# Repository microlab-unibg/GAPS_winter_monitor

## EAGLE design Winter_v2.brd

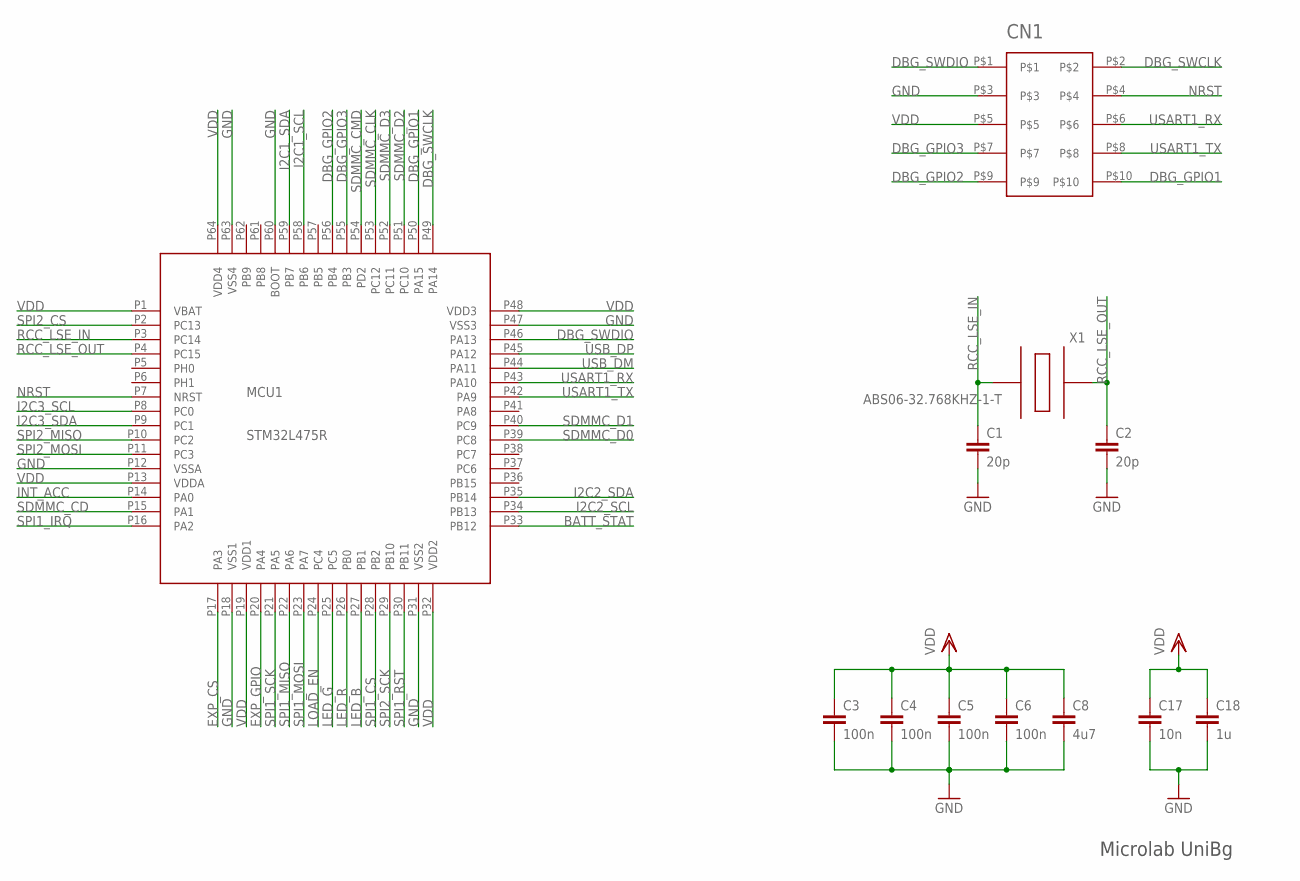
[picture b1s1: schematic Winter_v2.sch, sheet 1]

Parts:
C1, C2: 20p; C0402
C3, C4, C5, C6: 100n; C0402
C8: 4u7; C0402
C17: 10n; C0402
C18: 1u; C0402
CN1: FTSH-105TO; FTSH-105-XX
MCU1: STM32L475R; LQFP64
X1: ABS06-32.768KHZ-1-T; ABS06

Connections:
BATT_STAT: MCU1.P33 (PB12); also elsewhere on the board
DBG_GPIO1: CN1.P$10, MCU1.P50 (PA15)
DBG_GPIO2: CN1.P$9, MCU1.P56 (PB4)
DBG_GPIO3: CN1.P$7, MCU1.P55 (PB3)
DBG_SWCLK: CN1.P$2, MCU1.P49 (PA14)
DBG_SWDIO: CN1.P$1, MCU1.P46 (PA13)
EXP_CS: MCU1.P17 (PA3); also elsewhere on the board
EXP_GPIO: MCU1.P20 (PA4); also elsewhere on the board
GND: C1.P$2 (2), C2.P$2 (2), C3.P$2 (2), C4.P$2 (2), C5.P$2 (2), C6.P$2 (2), C8.P$2 (2), C17.P$2 (2), C18.P$2 (2), CN1.P$3, MCU1.P12 (VSSA), MCU1.P18 (VSS1), MCU1.P31 (VSS2), MCU1.P47 (VSS3), MCU1.P60 (BOOT), MCU1.P63 (VSS4); also elsewhere on the board
I2C1_SCL: MCU1.P58 (PB6); also elsewhere on the board
I2C1_SDA: MCU1.P59 (PB7); also elsewhere on the board
I2C2_SCL: MCU1.P34 (PB13); also elsewhere on the board
I2C2_SDA: MCU1.P35 (PB14); also elsewhere on the board
I2C3_SCL: MCU1.P8 (PC0); also elsewhere on the board
I2C3_SDA: MCU1.P9 (PC1); also elsewhere on the board
INT_ACC: MCU1.P14 (PA0); also elsewhere on the board
LED_B: MCU1.P27 (PB1); also elsewhere on the board
LED_G: MCU1.P25 (PC5); also elsewhere on the board
LED_R: MCU1.P26 (PB0); also elsewhere on the board
LOAD_EN: MCU1.P24 (PC4); also elsewhere on the board
NRST: CN1.P$4, MCU1.P7 (NRST)
RCC_LSE_IN: C1.P$1 (1), MCU1.P3 (PC14), X1.P1
RCC_LSE_OUT: C2.P$1 (1), MCU1.P4 (PC15), X1.P2
SDMMC_CD: MCU1.P15 (PA1); also elsewhere on the board
SDMMC_CLK: MCU1.P53 (PC12); also elsewhere on the board
SDMMC_CMD: MCU1.P54 (PD2); also elsewhere on the board
SDMMC_D0: MCU1.P39 (PC8); also elsewhere on the board
SDMMC_D1: MCU1.P40 (PC9); also elsewhere on the board
SDMMC_D2: MCU1.P51 (PC10); also elsewhere on the board
SDMMC_D3: MCU1.P52 (PC11); also elsewhere on the board
SPI1_CS: MCU1.P28 (PB2); also elsewhere on the board
SPI1_IRQ: MCU1.P16 (PA2); also elsewhere on the board
SPI1_MISO: MCU1.P22 (PA6); also elsewhere on the board
SPI1_MOSI: MCU1.P23 (PA7); also elsewhere on the board
SPI1_RST: MCU1.P30 (PB11); also elsewhere on the board
SPI1_SCK: MCU1.P21 (PA5); also elsewhere on the board
SPI2_CS: MCU1.P2 (PC13); also elsewhere on the board
SPI2_MISO: MCU1.P10 (PC2); also elsewhere on the board
SPI2_MOSI: MCU1.P11 (PC3); also elsewhere on the board
SPI2_SCK: MCU1.P29 (PB10); also elsewhere on the board
USART1_RX: CN1.P$6, MCU1.P43 (PA10)
USART1_TX: CN1.P$8, MCU1.P42 (PA9)
USB_DM: MCU1.P44 (PA11); also elsewhere on the board
USB_DP: MCU1.P45 (PA12); also elsewhere on the board
VDD: C3.P$1 (1), C4.P$1 (1), C5.P$1 (1), C6.P$1 (1), C8.P$1 (1), C17.P$1 (1), C18.P$1 (1), CN1.P$5, MCU1.P1 (VBAT), MCU1.P13 (VDDA), MCU1.P19 (VDD1), MCU1.P32 (VDD2), MCU1.P48 (VDD3), MCU1.P64 (VDD4); also elsewhere on the board

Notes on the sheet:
Microlab UniBg

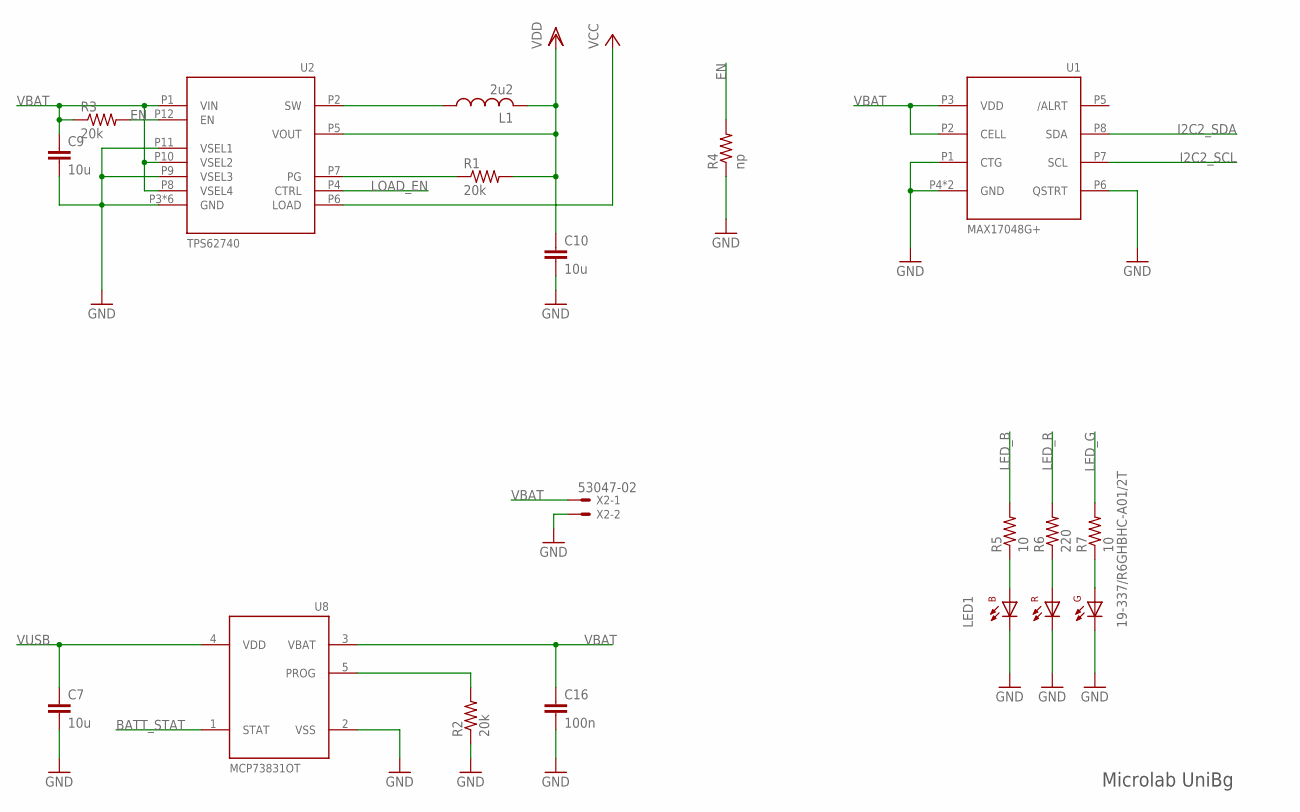
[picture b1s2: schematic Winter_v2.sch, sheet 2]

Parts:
C7, C9, C10: 10u; C0603
C16: 100n; C0402
L1: 2u2; C01005
LED1: 19-337/R6GHBHC-A01/2T
R1, R2, R3: 20k; 0402
R4: np; 0402
R5, R7: 10; 0402
R6: 220; 0402
U1: MAX17048G+; TDFN8-2X2
U2: TPS62740; R-PWSON-N12
U8: MCP73831OT; SOT23-5L
X2: 53047-02

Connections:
BATT_STAT: U8.1 (STAT); also elsewhere on the board
EN: R3.P$2 (2), R4.P$2 (2), U2.P12 (EN)
GND: C7.P$2 (2), C9.P$2 (2), C10.P$2 (2), C16.P$2 (2), LED1.P$1 (CB), LED1.P$2 (CR), LED1.P$3 (CG), R2.P$1 (1), R4.P$1 (1), U1.P1 (CTG), U1.P4 (GND), U1.P6 (QSTRT), U1.P9 (GND), U2.P3 (GND), U2.P9 (VSEL3), U2.P11 (VSEL1), U2.PG1 (GND), U2.PG2 (GND), U2.PG3 (GND), U2.PG4 (GND), U2.PG5 (GND), U8.2 (VSS), X2.2; also elsewhere on the board
I2C2_SCL: U1.P7 (SCL); also elsewhere on the board
I2C2_SDA: U1.P8 (SDA); also elsewhere on the board
LED_B: R5.P$2 (2); also elsewhere on the board
LED_G: R7.P$2 (2); also elsewhere on the board
LED_R: R6.P$2 (2); also elsewhere on the board
LOAD_EN: U2.P4 (CTRL); also elsewhere on the board
unnamed: L1.P$1 (1), U2.P2 (SW)
unnamed: R1.P$1 (1), U2.P7 (PG)
unnamed: LED1.P$4 (AB), R5.P$1 (1)
unnamed: LED1.P$5 (AR), R6.P$1 (1)
unnamed: LED1.P$6 (AG), R7.P$1 (1)
unnamed: R2.P$2 (2), U8.5 (PROG)
VBAT: C9.P$1 (1), C16.P$1 (1), R3.P$1 (1), U1.P2 (CELL), U1.P3 (VDD), U2.P1 (VIN), U2.P8 (VSEL4), U2.P10 (VSEL2), U8.3 (VBAT), X2.1; also elsewhere on the board
VCC: U2.P6 (LOAD); also elsewhere on the board
VDD: C10.P$1 (1), L1.P$2 (2), R1.P$2 (2), U2.P5 (VOUT); also elsewhere on the board
VUSB: C7.P$1 (1), U8.4 (VDD); also elsewhere on the board

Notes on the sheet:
Microlab UniBg

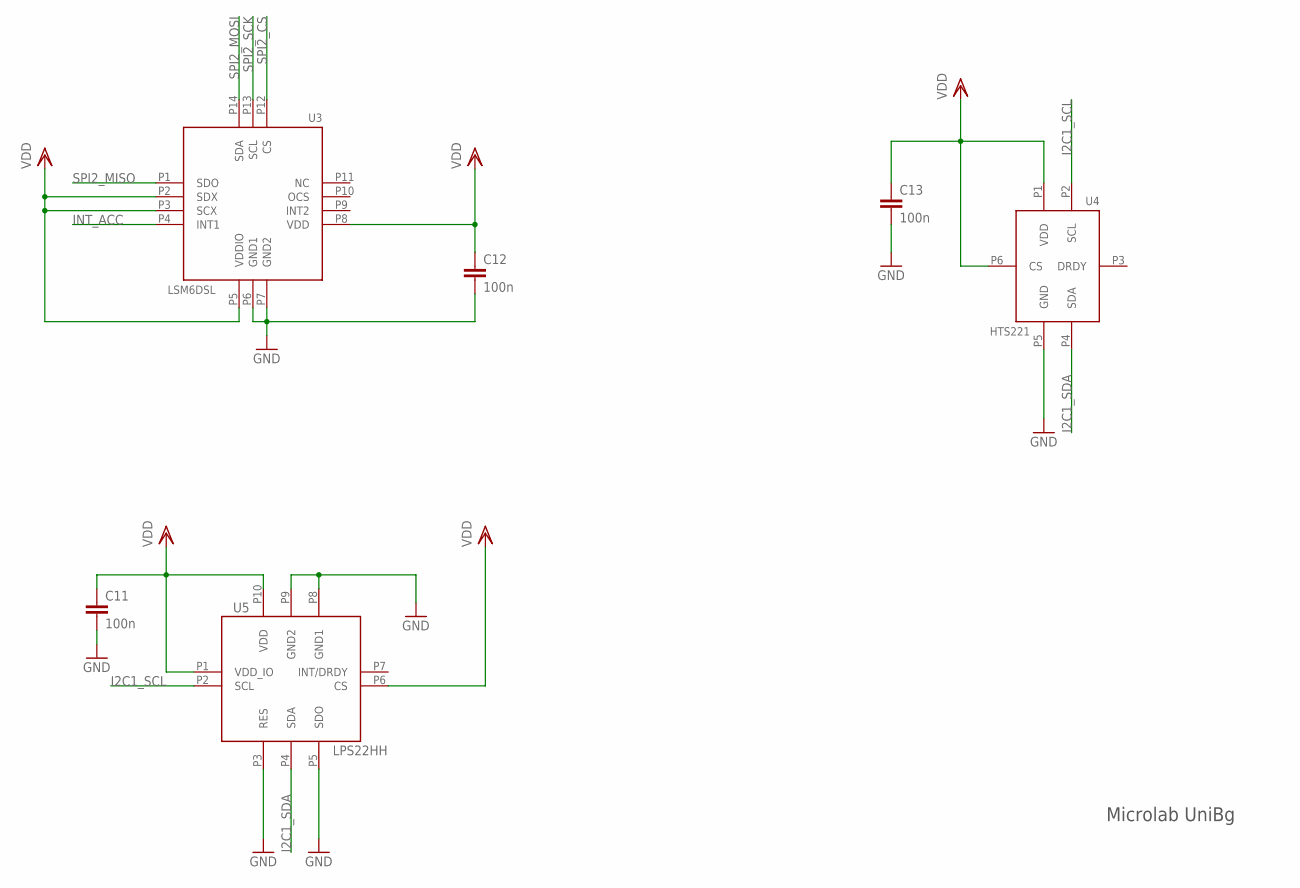
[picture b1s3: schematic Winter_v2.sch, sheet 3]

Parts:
C11, C12, C13: 100n; C0402
U3: LSM6DSL; LGA-14L
U4: HTS221; HCLGA-6L
U5: LPS22HH; HLGA-10L

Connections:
GND: C11.P$2 (2), C12.P$2 (2), C13.P$2 (2), U3.P6 (GND1), U3.P7 (GND2), U4.P5 (GND), U5.P3 (RES), U5.P5 (SDO), U5.P8 (GND1), U5.P9 (GND2); also elsewhere on the board
I2C1_SCL: U4.P2 (SCL), U5.P2 (SCL); also elsewhere on the board
I2C1_SDA: U4.P4 (SDA), U5.P4 (SDA); also elsewhere on the board
INT_ACC: U3.P4 (INT1); also elsewhere on the board
SPI2_CS: U3.P12 (CS); also elsewhere on the board
SPI2_MISO: U3.P1 (SDO); also elsewhere on the board
SPI2_MOSI: U3.P14 (SDA); also elsewhere on the board
SPI2_SCK: U3.P13 (SCL); also elsewhere on the board
VDD: C11.P$1 (1), C12.P$1 (1), C13.P$1 (1), U3.P2 (SDX), U3.P3 (SCX), U3.P5 (VDDIO), U3.P8 (VDD), U4.P1 (VDD), U4.P6 (CS), U5.P1 (VDD_IO), U5.P6 (CS), U5.P10 (VDD); also elsewhere on the board

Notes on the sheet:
Microlab UniBg

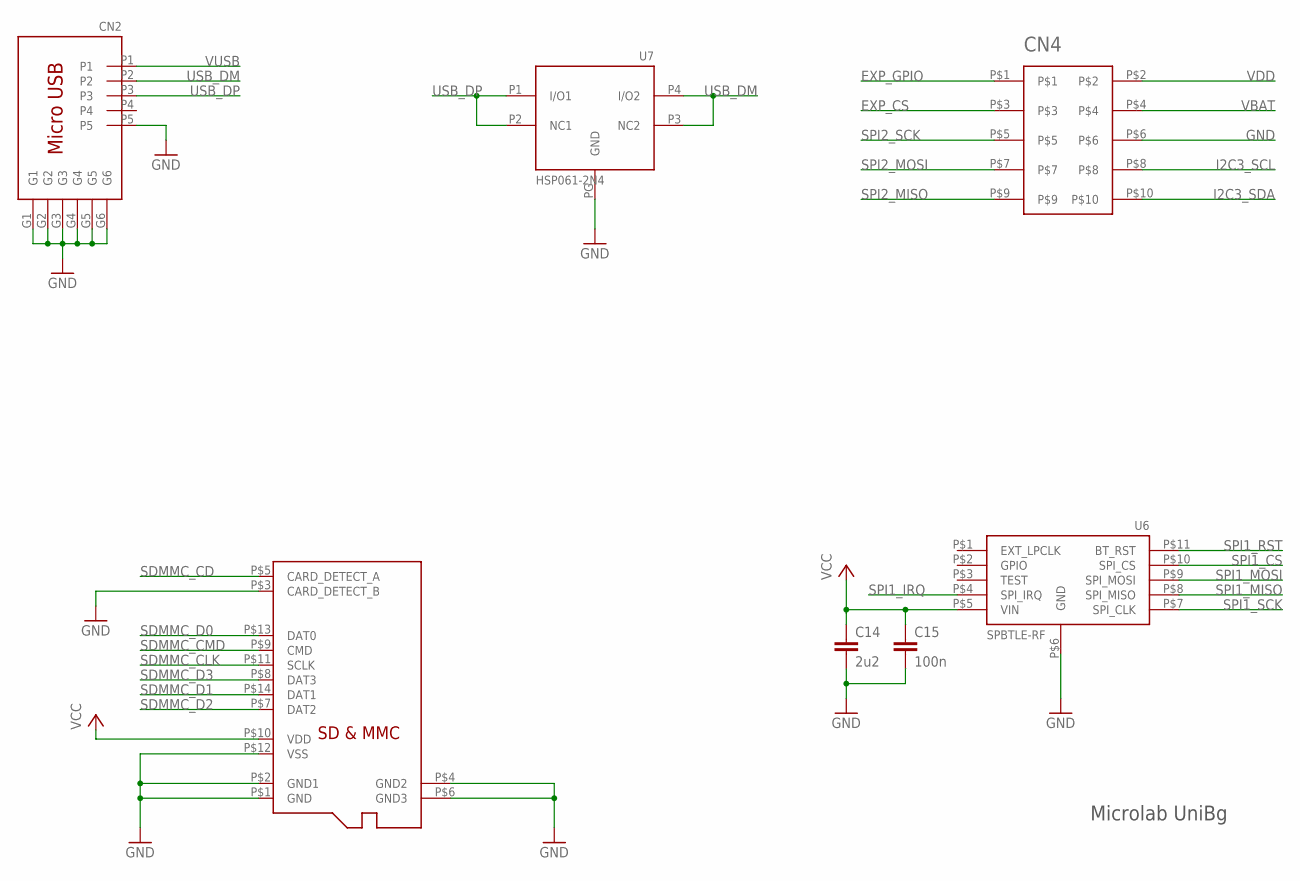
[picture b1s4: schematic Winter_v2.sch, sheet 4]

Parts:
C14: 2u2; C0402
C15: 100n; C0402
CN2: USB3075
CN3: MICRO_SD-5025700893; 5025700893
CN4: FTSH-105TO; FTSH-105-XX
U6: SPBTLE-RF
U7: HSP061-2N4; μQFN-4L

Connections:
EXP_CS: CN4.P$3; also elsewhere on the board
EXP_GPIO: CN4.P$1; also elsewhere on the board
GND: C14.P$2 (2), C15.P$2 (2), CN2.G1, CN2.G2, CN2.G3, CN2.G4, CN2.G5, CN2.G6, CN2.P5, CN3.P$1 (GND), CN3.P$2 (GND1), CN3.P$3 (CARD_DETECT_B), CN3.P$4 (GND2), CN3.P$6 (GND3), CN3.P$12 (VSS), CN4.P$6, U6.P$6 (GND), U7.PG (GND); also elsewhere on the board
I2C3_SCL: CN4.P$8; also elsewhere on the board
I2C3_SDA: CN4.P$10; also elsewhere on the board
SDMMC_CD: CN3.P$5 (CARD_DETECT_A); also elsewhere on the board
SDMMC_CLK: CN3.P$11 (SCLK); also elsewhere on the board
SDMMC_CMD: CN3.P$9 (CMD); also elsewhere on the board
SDMMC_D0: CN3.P$13 (DAT0); also elsewhere on the board
SDMMC_D1: CN3.P$14 (DAT1); also elsewhere on the board
SDMMC_D2: CN3.P$7 (DAT2); also elsewhere on the board
SDMMC_D3: CN3.P$8 (DAT3); also elsewhere on the board
SPI1_CS: U6.P$10 (SPI_CS); also elsewhere on the board
SPI1_IRQ: U6.P$4 (SPI_IRQ); also elsewhere on the board
SPI1_MISO: U6.P$8 (SPI_MISO); also elsewhere on the board
SPI1_MOSI: U6.P$9 (SPI_MOSI); also elsewhere on the board
SPI1_RST: U6.P$11 (BT_RST); also elsewhere on the board
SPI1_SCK: U6.P$7 (SPI_CLK); also elsewhere on the board
SPI2_MISO: CN4.P$9; also elsewhere on the board
SPI2_MOSI: CN4.P$7; also elsewhere on the board
SPI2_SCK: CN4.P$5; also elsewhere on the board
USB_DM: CN2.P2, U7.P3 (NC2), U7.P4 (I/O2); also elsewhere on the board
USB_DP: CN2.P3, U7.P1 (I/O1), U7.P2 (NC1); also elsewhere on the board
VBAT: CN4.P$4; also elsewhere on the board
VCC: C14.P$1 (1), C15.P$1 (1), CN3.P$10 (VDD), U6.P$5 (VIN); also elsewhere on the board
VDD: CN4.P$2; also elsewhere on the board
VUSB: CN2.P1; also elsewhere on the board

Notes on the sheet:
Microlab UniBg

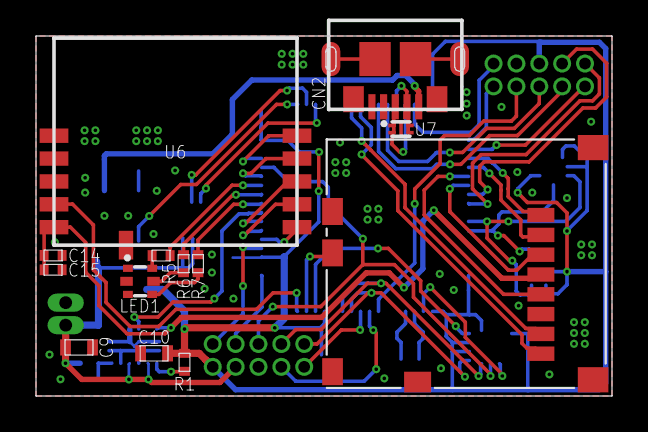
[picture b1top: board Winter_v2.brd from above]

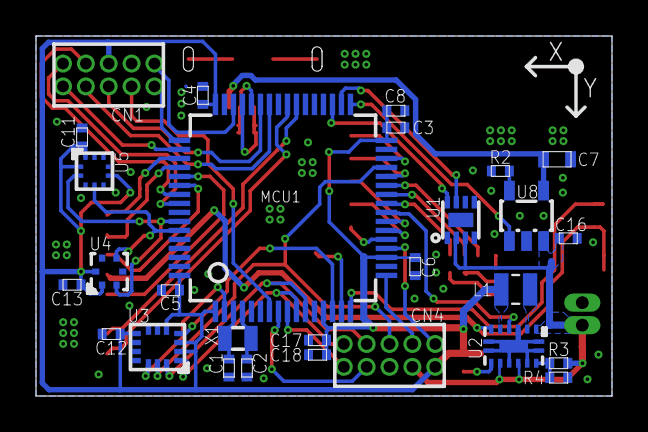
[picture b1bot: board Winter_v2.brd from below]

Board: 2 copper layers, 32.0 x 20.0 mm, 43 parts (28 on the bottom side), 55 nets.

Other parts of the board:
DRILEGEND: DRILEGEND

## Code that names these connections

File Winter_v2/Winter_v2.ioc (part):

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Mcu.Name=STM32L475R(C-E-G)Tx
Mcu.Package=LQFP64
Mcu.UserName=STM32L475RGTx
PA0.GPIOParameters=GPIO_Label
PA0.GPIO_Label=INT_ACC
PA0.Signal=GPXTI0
PA1.GPIOParameters=GPIO_PuPd,GPIO_Label
PA1.GPIO_Label=SD_CD
PA1.GPIO_PuPd=GPIO_PULLUP
PA1.Signal=GPIO_Input
PA13\ (JTMS-SWDIO).Mode=Serial_Wire
PA13\ (JTMS-SWDIO).Signal=SYS_JTMS-SWDIO
PA14\ (JTCK-SWCLK).Mode=Serial_Wire
PA14\ (JTCK-SWCLK).Signal=SYS_JTCK-SWCLK
PA15\ (JTDI).GPIOParameters=GPIO_Label
PA15\ (JTDI).GPIO_Label=DBG_GPIO1
PA15\ (JTDI).Signal=GPIO_Output
PA2.GPIOParameters=GPIO_PuPd,GPIO_Label
PA2.GPIO_Label=BLE_IRQ
PA2.GPIO_PuPd=GPIO_NOPULL
PA2.Signal=GPXTI2
PA3.GPIOParameters=PinState,GPIO_PuPd,GPIO_Label
PA3.GPIO_Label=EXP_CS
PA3.GPIO_PuPd=GPIO_PULLUP
PA3.PinState=GPIO_PIN_SET
PA3.Signal=GPIO_Output
PA4.GPIOParameters=GPIO_Label
PA4.GPIO_Label=EXP_GPIO
PA4.Signal=GPIO_Input
PA5.GPIOParameters=GPIO_Label
PA5.GPIO_Label=BLE_SCK
PA5.Mode=Full_Duplex_Master
PA5.Signal=SPI1_SCK
PA6.GPIOParameters=GPIO_Label
PA6.GPIO_Label=BLE_MISO
PA6.Mode=Full_Duplex_Master
PA6.Signal=SPI1_MISO
PA7.GPIOParameters=GPIO_Label
PA7.GPIO_Label=BLE_MOSI
PA7.Mode=Full_Duplex_Master
PA7.Signal=SPI1_MOSI
PB0.GPIOParameters=GPIO_Label
PB0.GPIO_Label=LED_RED
PB0.Signal=GPIO_Output
PB1.GPIOParameters=GPIO_Label
PB1.GPIO_Label=LED_BLUE
PB1.Signal=GPIO_Output
PB10.GPIOParameters=GPIO_Label
PB10.GPIO_Label=MISC_SCK
PB10.Mode=Full_Duplex_Master
PB10.Signal=SPI2_SCK
PB11.GPIOParameters=PinState,GPIO_Label
PB11.GPIO_Label=BLE_RST
PB11.PinState=GPIO_PIN_RESET
PB11.Signal=GPIO_Output
PB12.GPIOParameters=GPIO_Label
PB12.GPIO_Label=BATT_STAT
PB12.Signal=GPIO_Input
PB13.GPIOParameters=GPIO_Label
PB13.GPIO_Label=GAS_SCL
PB13.Mode=I2C
PB13.Signal=I2C2_SCL
PB14.GPIOParameters=GPIO_Label
PB14.GPIO_Label=GAS_SDA
PB14.Mode=I2C
PB14.Signal=I2C2_SDA
PB2.GPIOParameters=GPIO_Label
PB2.GPIO_Label=BLE_CS
PB2.Signal=GPIO_Analog
PB3\ (JTDO-TRACESWO).GPIOParameters=GPIO_Label
PB3\ (JTDO-TRACESWO).GPIO_Label=DBG_GPIO3
PB3\ (JTDO-TRACESWO).Signal=GPIO_Input
PB4\ (NJTRST).GPIOParameters=GPIO_Label
PB4\ (NJTRST).GPIO_Label=DBG_GPIO2
PB4\ (NJTRST).Signal=GPIO_Input
PB6.GPIOParameters=GPIO_Label
PB6.GPIO_Label=ENV_SCL
PB6.Mode=I2C
PB6.Signal=I2C1_SCL
PB7.GPIOParameters=GPIO_Label
PB7.GPIO_Label=ENV_SDA
PB7.Mode=I2C
PB7.Signal=I2C1_SDA
PC0.GPIOParameters=GPIO_Label
PC0.GPIO_Label=EXP_SCL
PC0.Mode=I2C
PC0.Signal=I2C3_SCL
PC1.GPIOParameters=GPIO_Label
PC1.GPIO_Label=EXP_SDA
PC1.Mode=I2C
PC1.Signal=I2C3_SDA
PC13.GPIOParameters=PinState,GPIO_PuPd,GPIO_Label
PC13.GPIO_Label=MOT_CS
PC13.GPIO_PuPd=GPIO_PULLUP
PC13.PinState=GPIO_PIN_SET
PC13.Signal=GPIO_Output
PC14-OSC32_IN\ (PC14).Mode=LSE-External-Oscillator
PC14-OSC32_IN\ (PC14).Signal=RCC_OSC32_IN
PC15-OSC32_OUT\ (PC15).Mode=LSE-External-Oscillator
PC15-OSC32_OUT\ (PC15).Signal=RCC_OSC32_OUT
PC2.GPIOParameters=GPIO_Label
PC2.GPIO_Label=MISC_MISO
PC2.Mode=Full_Duplex_Master
PC2.Signal=SPI2_MISO
PC3.GPIOParameters=GPIO_Label
PC3.GPIO_Label=MISC_MOSI
PC3.Mode=Full_Duplex_Master
PC3.Signal=SPI2_MOSI
PC4.GPIOParameters=GPIO_Label
PC4.GPIO_Label=LOAD_EN
PC4.Signal=GPIO_Output
PC5.GPIOParameters=GPIO_Label
PC5.GPIO_Label=LED_GREEN
PC5.Signal=GPIO_Output
RCC.HSE_VALUE=8000000
RCC.SYSCLKFreq_VALUE=8000000
board=custom

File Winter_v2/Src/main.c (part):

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  HAL_GPIO_WritePin(MOT_CS_GPIO_Port, MOT_CS_Pin, GPIO_PIN_SET);

  /*Configure GPIO pin Output Level */
  HAL_GPIO_WritePin(EXP_CS_GPIO_Port, EXP_CS_Pin, GPIO_PIN_SET);

  /*Configure GPIO pin Output Level */
  HAL_GPIO_WritePin(GPIOC, LOAD_EN_Pin|LED_GREEN_Pin, GPIO_PIN_RESET);

  /*Configure GPIO pin Output Level */
  HAL_GPIO_WritePin(GPIOB, LED_RED_Pin|LED_BLUE_Pin|BLE_RST_Pin, GPIO_PIN_RESET);

  /*Configure GPIO pin Output Level */
  HAL_GPIO_WritePin(DBG_GPIO1_GPIO_Port, DBG_GPIO1_Pin, GPIO_PIN_RESET);

  /*Configure GPIO pin : MOT_CS_Pin */
  GPIO_InitStruct.Pin = MOT_CS_Pin;
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  GPIO_InitStruct.Pull = GPIO_NOPULL;
  HAL_GPIO_Init(GPIOH, &GPIO_InitStruct);

  /*Configure GPIO pins : INT_ACC_Pin BLE_IRQ_Pin */
  GPIO_InitStruct.Pin = INT_ACC_Pin|BLE_IRQ_Pin;
  GPIO_InitStruct.Mode = GPIO_MODE_IT_RISING;
  GPIO_InitStruct.Pull = GPIO_NOPULL;
  HAL_GPIO_Init(GPIOA, &GPIO_InitStruct);
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  GPIO_InitStruct.Pull = GPIO_PULLUP;
  HAL_GPIO_Init(SD_CD_GPIO_Port, &GPIO_InitStruct);

  /*Configure GPIO pin : EXP_CS_Pin */
  GPIO_InitStruct.Pin = EXP_CS_Pin;
  GPIO_InitStruct.Mode = GPIO_MODE_OUTPUT_PP;
  GPIO_InitStruct.Pull = GPIO_PULLUP;
  GPIO_InitStruct.Speed = GPIO_SPEED_FREQ_LOW;
  HAL_GPIO_Init(EXP_CS_GPIO_Port, &GPIO_InitStruct);

  /*Configure GPIO pin : EXP_GPIO_Pin */
  GPIO_InitStruct.Pin = EXP_GPIO_Pin;
  GPIO_InitStruct.Mode = GPIO_MODE_INPUT;
  GPIO_InitStruct.Pull = GPIO_NOPULL;
  HAL_GPIO_Init(EXP_GPIO_GPIO_Port, &GPIO_InitStruct);

  /*Configure GPIO pins : LOAD_EN_Pin LED_GREEN_Pin */
  GPIO_InitStruct.Pin = LOAD_EN_Pin|LED_GREEN_Pin;
  GPIO_InitStruct.Mode = GPIO_MODE_OUTPUT_PP;
  GPIO_InitStruct.Pull = GPIO_NOPULL;
  GPIO_InitStruct.Speed = GPIO_SPEED_FREQ_LOW;
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  GPIO_InitStruct.Pull = GPIO_NOPULL;
  HAL_GPIO_Init(GPIOB, &GPIO_InitStruct);

  /*Configure GPIO pins : BATT_STAT_Pin DBG_GPIO3_Pin DBG_GPIO2_Pin */
  GPIO_InitStruct.Pin = BATT_STAT_Pin|DBG_GPIO3_Pin|DBG_GPIO2_Pin;
  GPIO_InitStruct.Mode = GPIO_MODE_INPUT;
  GPIO_InitStruct.Pull = GPIO_NOPULL;
  HAL_GPIO_Init(GPIOB, &GPIO_InitStruct);

  /*Configure GPIO pins : PC6 PC7 PC8 PC9
                           PC10 PC11 PC12 */
  GPIO_InitStruct.Pin = GPIO_PIN_6|GPIO_PIN_7|GPIO_PIN_8|GPIO_PIN_9
                          |GPIO_PIN_10|GPIO_PIN_11|GPIO_PIN_12;
  GPIO_InitStruct.Mode = GPIO_MODE_ANALOG;
  GPIO_InitStruct.Pull = GPIO_NOPULL;
  HAL_GPIO_Init(GPIOC, &GPIO_InitStruct);

  /*Configure GPIO pins : PA8 PA9 PA10 PA11
                           PA12 */
  GPIO_InitStruct.Pin = GPIO_PIN_8|GPIO_PIN_9|GPIO_PIN_10|GPIO_PIN_11
                          |GPIO_PIN_12;
  GPIO_InitStruct.Mode = GPIO_MODE_ANALOG;
  GPIO_InitStruct.Pull = GPIO_NOPULL;
  HAL_GPIO_Init(GPIOA, &GPIO_InitStruct);

  /*Configure GPIO pin : DBG_GPIO1_Pin */
  GPIO_InitStruct.Pin = DBG_GPIO1_Pin;
  GPIO_InitStruct.Mode = GPIO_MODE_OUTPUT_PP;
  GPIO_InitStruct.Pull = GPIO_NOPULL;
  GPIO_InitStruct.Speed = GPIO_SPEED_FREQ_LOW;
  HAL_GPIO_Init(DBG_GPIO1_GPIO_Port, &GPIO_InitStruct);

  /*Configure GPIO pin : PD2 */
  GPIO_InitStruct.Pin = GPIO_PIN_2;
  GPIO_InitStruct.Mode = GPIO_MODE_ANALOG;
  GPIO_InitStruct.Pull = GPIO_NOPULL;
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			HAL_GPIO_WritePin(MOT_CS_GPIO_Port, MOT_CS_Pin, GPIO_PIN_SET);
			break;
		case SPI_EXP:
			HAL_GPIO_WritePin(EXP_CS_GPIO_Port, EXP_CS_Pin, GPIO_PIN_RESET);
			res |= HAL_SPI_Transmit(&hspi2, pData, Size, 100);
			HAL_GPIO_WritePin(EXP_CS_GPIO_Port, EXP_CS_Pin, GPIO_PIN_SET);
		default:
			res = HAL_ERROR;
			break;
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			HAL_GPIO_WritePin(MOT_CS_GPIO_Port, MOT_CS_Pin, GPIO_PIN_SET);
			break;
		case SPI_EXP:
			HAL_GPIO_WritePin(EXP_CS_GPIO_Port, EXP_CS_Pin, GPIO_PIN_RESET);
			res |= HAL_SPI_Transmit(&hspi2, &RegAddress, 1, 100);
			res |= HAL_SPI_Receive(&hspi2, pData, Size, 100);
			HAL_GPIO_WritePin(EXP_CS_GPIO_Port, EXP_CS_Pin, GPIO_PIN_SET);
			break;
		default:
			res = HAL_ERROR;
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	/* EXTI interrupt deinit*/
	HAL_NVIC_DisableIRQ(EXTI2_IRQn);

	/*Configure GPIO pins : PA1 PA2 PA3 PA4 PA15 */
	GPIO_InitStruct.Pin = SD_CD_Pin | BLE_IRQ_Pin | EXP_CS_Pin | EXP_GPIO_Pin
			| DBG_GPIO1_Pin;
	GPIO_InitStruct.Mode = GPIO_MODE_ANALOG;
	GPIO_InitStruct.Pull = GPIO_NOPULL;
	HAL_GPIO_Init(GPIOA, &GPIO_InitStruct);

	/*Configure GPIO pins : PB0 PB1 PB2 PB3 PB4 PB11 PB12 */
	GPIO_InitStruct.Pin = LED_RED_Pin | LED_BLUE_Pin | BLE_CS_Pin
			| DBG_GPIO3_Pin | DBG_GPIO2_Pin | BLE_RST_Pin | BATT_STAT_Pin;
	GPIO_InitStruct.Mode = GPIO_MODE_ANALOG;
	GPIO_InitStruct.Pull = GPIO_NOPULL;
	HAL_GPIO_Init(GPIOB, &GPIO_InitStruct);

	/*Configure GPIO pins : PC4 PC5 PC8 PC9 PC10 PC11 PC12 PC13 */
	GPIO_InitStruct.Pin = LOAD_EN_Pin | LED_GREEN_Pin | MOT_CS_Pin;
	GPIO_InitStruct.Mode = GPIO_MODE_ANALOG;
	GPIO_InitStruct.Pull = GPIO_NOPULL;
	HAL_GPIO_Init(GPIOC, &GPIO_InitStruct);

	/*Configure GPIO pins : PD2 */
	//GPIO_InitStruct.Pin = SD_CMD_Pin;
	GPIO_InitStruct.Mode = GPIO_MODE_ANALOG;
	GPIO_InitStruct.Pull = GPIO_NOPULL;
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
	// Set SDA and SCL pins of I2C1 e I2C2 to PUSH PULL with HIGH level
	// (alternatively, OPEN DRAIN with PULL-UP)
	/*Configure GPIO pins : PD2 */
	HAL_GPIO_WritePin(GPIOB,
			ENV_SCL_Pin | ENV_SDA_Pin | GAS_SCL_Pin | GAS_SDA_Pin,
			GPIO_PIN_SET);
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
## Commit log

2022-06-06 humidity firmware
2022-06-06 add schematic and layout
2022-07-21 Update firmware: wakeup through RTC

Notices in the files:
Winter_v2/Src/main.c:
© Copyright (c) 2020 STMicroelectronics.
All rights reserved.
This software component is licensed by ST under BSD 3-Clause license,
the "License"; You may not use this file except in compliance with the
License. You may obtain a copy of the License at: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
(C) COPYRIGHT STMicroelectronics *****END OF FILE
